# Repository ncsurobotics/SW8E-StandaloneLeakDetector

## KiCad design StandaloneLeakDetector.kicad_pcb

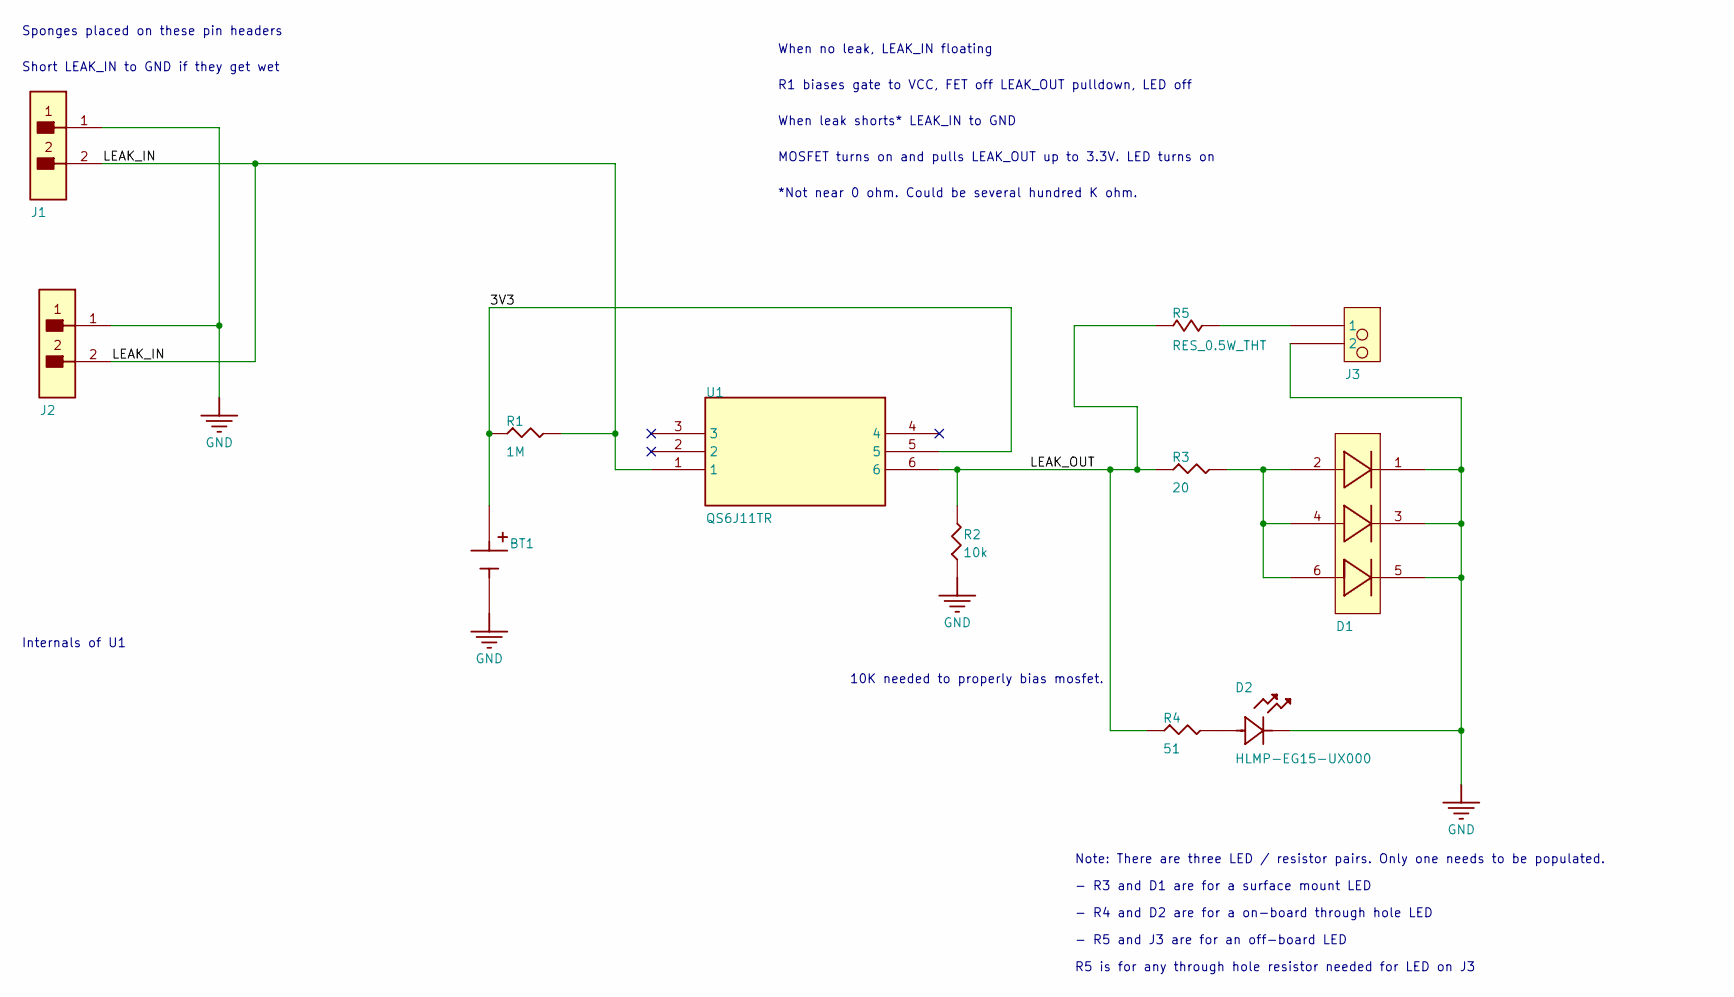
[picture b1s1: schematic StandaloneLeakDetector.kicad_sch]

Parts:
BT1: BAT-HLD-005-THM; BAT_BAT-HLD-005-THM; Part Number BAT-HLD-005-THM
D1: SMTL6-RC; Part Number SMTL6-RC
D2: HLMP-EG15-UX000; LED_AVAGO_HLMP_XX15_AVA; Part Number HLMP-EG15-UX000
J1, J2: TSW-102-07-L-S; FP-TSW-102-07-L-S-MFG; Part Number TSW-102-07-L-S
J3: Header; 1x2 Header
R1: 1M; SMD-0805-RES; Part Number ERJ-6ENF1004V
R2: 10k; SMD-0805-RES; Part Number ERJ-6ENF1002V
R3: 20; SMD-0805-RES; Part Number ERJ-6ENF20R0V
R4: 51; SMD-0805-RES; Part Number ERJ-6GEYJ510V
R5: RES_0.5W_THT
U1: QS6J11TR; TRANS_QS6_ROM; Part Number QS6J11TR

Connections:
/3V3: BT1.P1 (POS), BT1.P2 (POS), R1.1, U1.5
/LEAK_IN: J1.2, J2.2, R1.2, U1.1
/LEAK_OUT: R2.2, R3.1, R4.1, R5.1, U1.6
GND: BT1.N (NEG), D1.1, D1.3, D1.5, D2.1, J1.1, J2.1, J3.2, R2.1
unnamed: D1.2, D1.4, D1.6, R3.2
unnamed: D2.2, R4.2
unnamed: J3.1, R5.2

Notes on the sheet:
R5 is for any through hole resistor needed for LED on J3
- R3 and D1 are for a surface mount LED
10K needed to properly bias mosfet.
- R5 and J3 are for an off-board LED
Note: There are three LED / resistor pairs. Only one needs to be populated.
When no leak, LEAK_IN floating
- R4 and D2 are for a on-board through hole LED
Internals of U1
R1 biases gate to VCC, FET off LEAK_OUT pulldown, LED off
Sponges placed on these pin headers
MOSFET turns on and pulls LEAK_OUT up to 3.3V. LED turns on
*Not near 0 ohm. Could be several hundred K ohm.
When leak shorts* LEAK_IN to GND
Short LEAK_IN to GND if they get wet

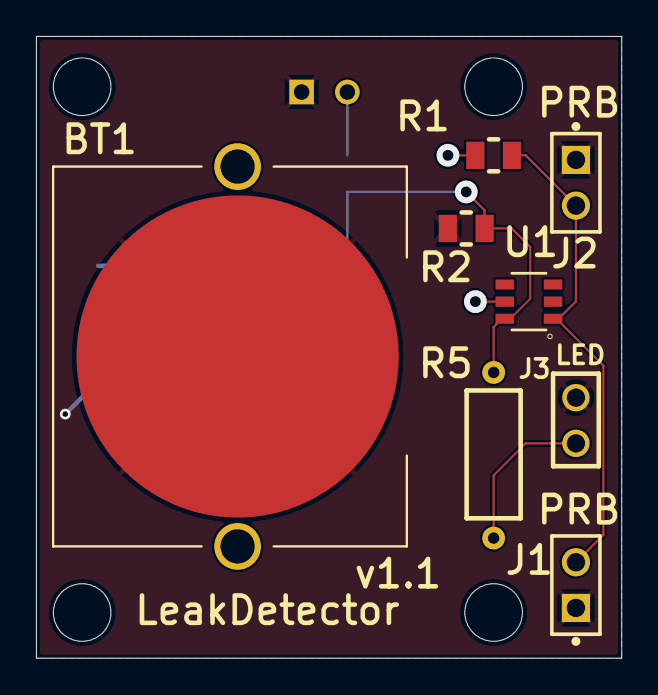
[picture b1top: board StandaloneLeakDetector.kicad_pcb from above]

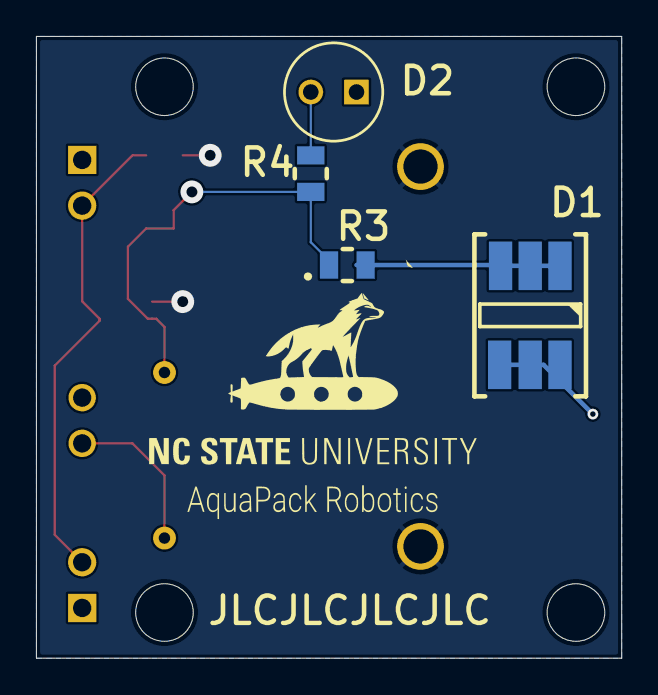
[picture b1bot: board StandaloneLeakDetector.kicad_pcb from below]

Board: 2 copper layers, 32.5 x 34.5 mm, 12 parts (4 on the bottom side), 7 nets.

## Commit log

2022-05-22 Add simulation, schematic, and first revision pcb
2022-05-22 Updated header pin order on schematic. Fixed and finished PCB. Using rules for JLC 2 layer 1oz board
2022-05-22 Change LED resistor and add info about power consumption in txt document
2022-05-22 Removed simulation results from repo
2022-05-23 Add mounting holes
2022-05-23 Add pcb name and version silkscreen
2022-05-24 Added logos to PCB and added BOM
2022-05-24 Added space in board name
2022-05-24 Moved logo to clear via
2022-06-29 Added other LED options
2022-06-30 Added two more LED options
2022-06-30 Add project changes not saved in last commit
2022-06-30 Updated power calculations notes for three led options
2022-06-30 Add ordering bom
2022-06-30 Condensed the board
2022-06-30 Added board outline
2023-04-11 Converted board from Altium to kicad
2023-06-05 Add license
2023-07-04 Update gitignore for kicad
2023-07-04 Fix footprint associations
2023-07-04 Remove imported symbol table fields
2023-07-04 Update board settings from template
2023-07-04 Mark mounting holes as 'not in schematic'

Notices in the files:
parts and their libraries:
COPYRIGHT: Copyright (C) 2022 Ultra Librarian. All rights reserved.
